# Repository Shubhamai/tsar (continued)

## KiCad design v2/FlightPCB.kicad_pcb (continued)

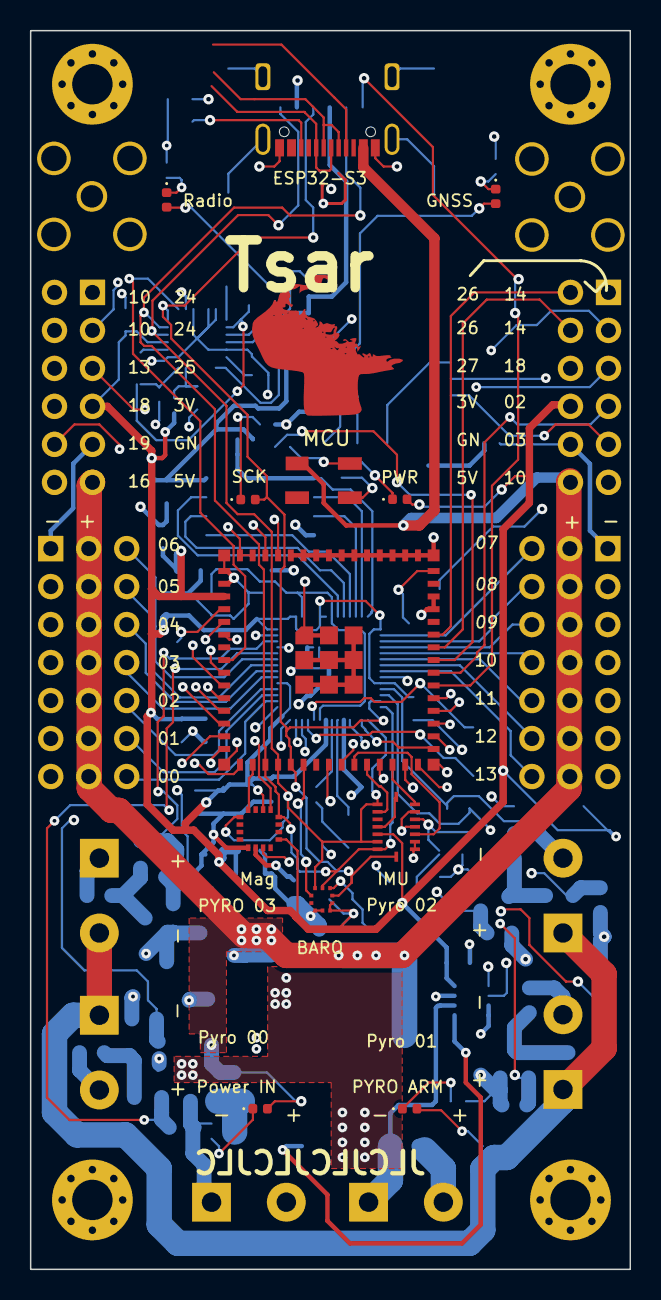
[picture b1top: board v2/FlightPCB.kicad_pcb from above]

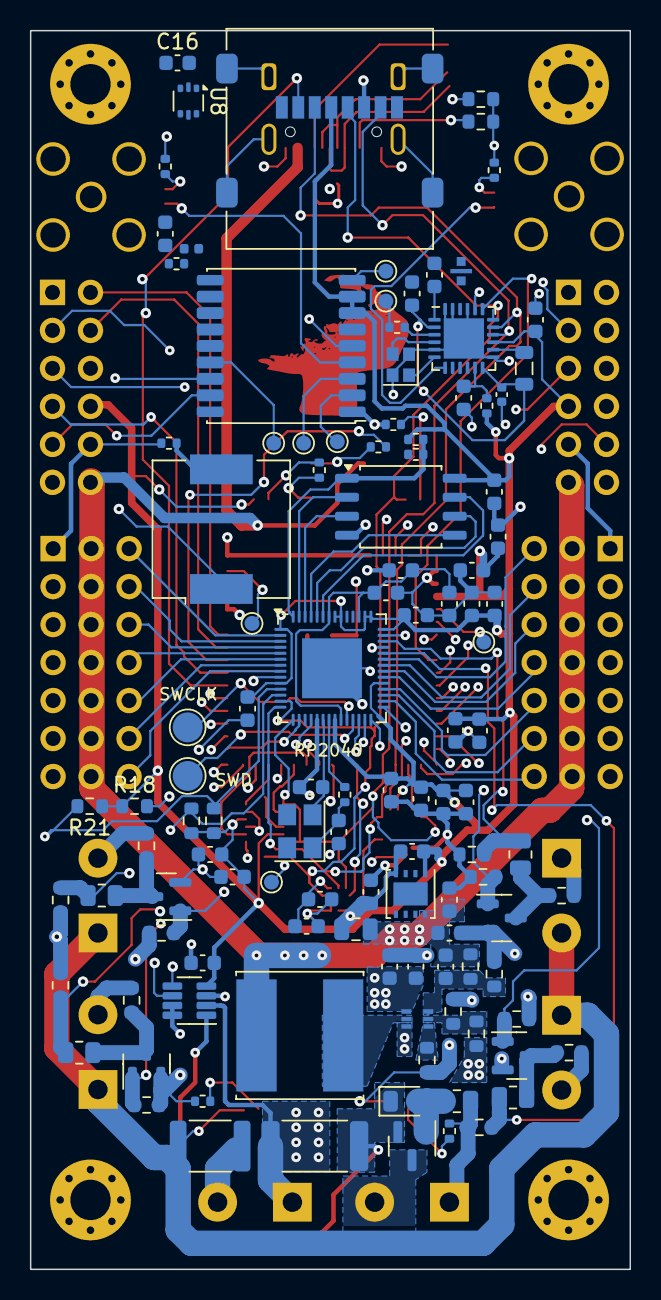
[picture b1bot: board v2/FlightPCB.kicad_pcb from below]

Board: 4 copper layers, 40.1 x 82.8 mm, 142 parts (114 on the bottom side), 124 nets.

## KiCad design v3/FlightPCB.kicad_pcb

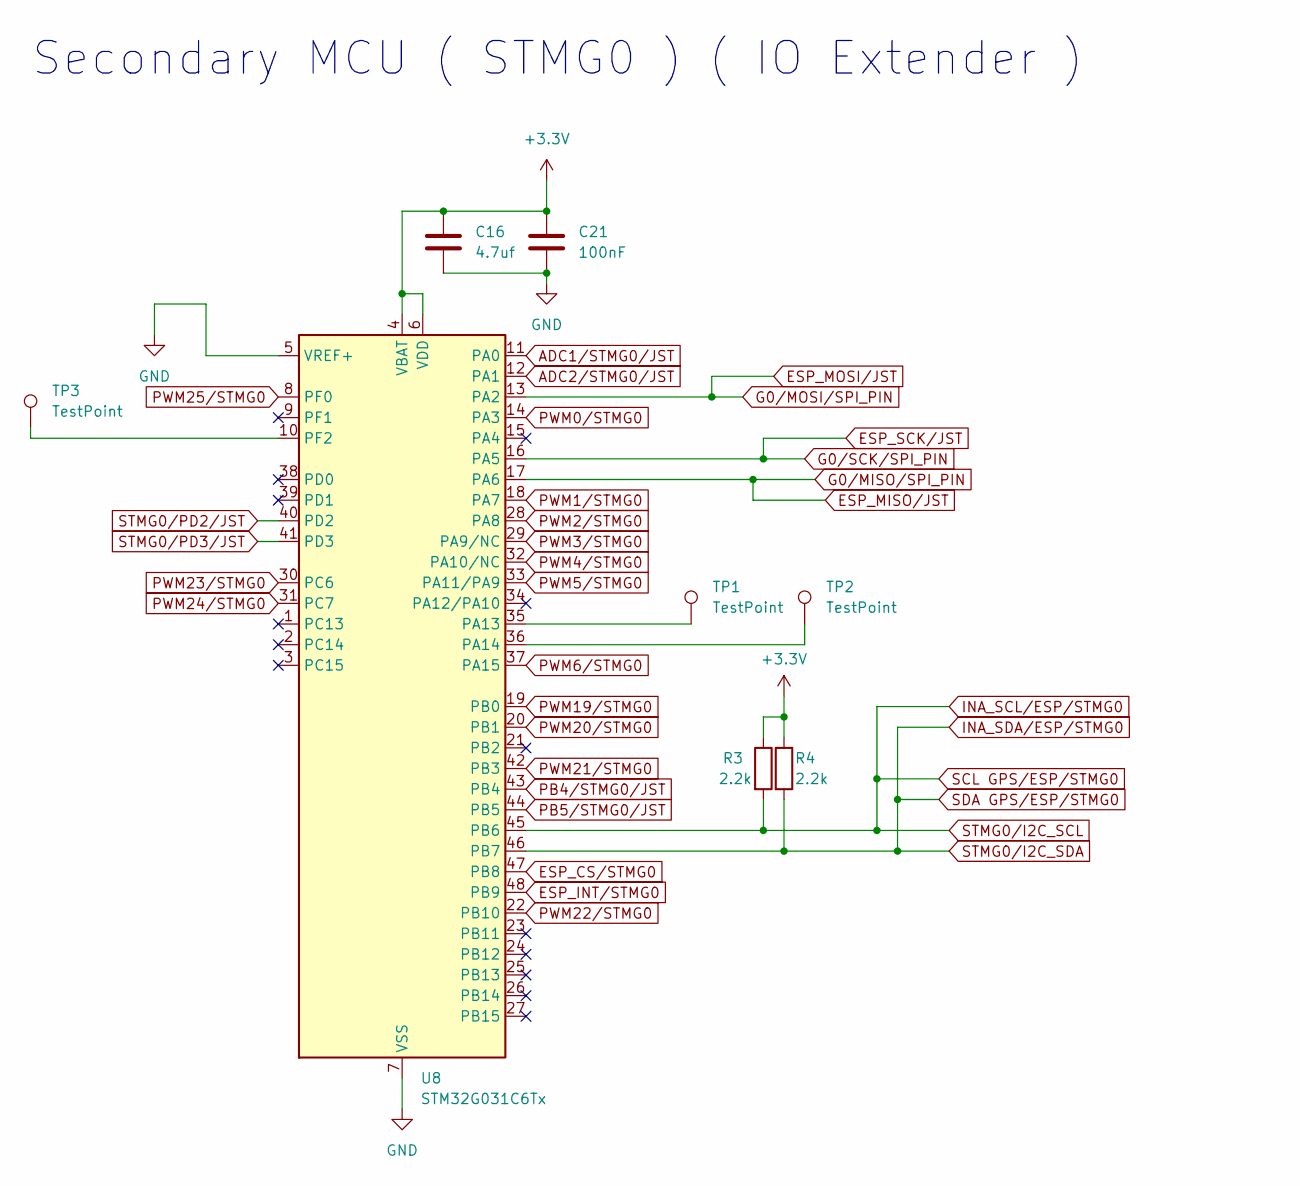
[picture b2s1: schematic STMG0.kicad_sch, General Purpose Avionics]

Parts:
C16: 4.7uf; C_0402_1005Metric
C21: 100nF; C_0402_1005Metric
R3, R4: 2.2k; R_0603_1608Metric
TP1, TP2, TP3: TestPoint; TestPoint_Pad_D1.0mm
U8: STM32G031C6Tx; LQFP-48_7x7mm_P0.5mm

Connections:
+3.3V: C16.1, C21.1, R3.1, R4.1, U8.4 (VBAT), U8.6 (VDD); also elsewhere on the board
ADC1/STMG0/JST: U8.11 (PA0); also elsewhere on the board
ADC2/STMG0/JST: U8.12 (PA1); also elsewhere on the board
BARO_MISO/ESP: U8.17 (PA6); also elsewhere on the board
BARO_MOSI/ESP: U8.13 (PA2); also elsewhere on the board
BARO_SCK/ESP: U8.16 (PA5); also elsewhere on the board
BatteryTerminal-: C16.2, C21.2, U8.5 (VREF+), U8.7 (VSS); also elsewhere on the board
ESP_CS/STMG0: U8.47 (PB8); also elsewhere on the board
ESP_INT/STMG0: U8.48 (PB9); also elsewhere on the board
ESP_SCL/Headers/JST: R3.2, U8.45 (PB6); also elsewhere on the board
ESP_SDA/Headers/JST: R4.2, U8.46 (PB7); also elsewhere on the board
unnamed: TP1.1, U8.35 (PA13)
unnamed: TP2.1, U8.36 (PA14)
unnamed: TP3.1, U8.10 (PF2)
PB4/STMG0/JST: U8.43 (PB4); also elsewhere on the board
PB5/STMG0/JST: U8.44 (PB5); also elsewhere on the board
PWM0/STMG0: U8.14 (PA3); also elsewhere on the board
PWM1/STMG0: U8.18 (PA7); also elsewhere on the board
PWM2/STMG0: U8.28 (PA8); also elsewhere on the board
PWM3/STMG0: U8.29 (PA9/NC); also elsewhere on the board
PWM4/STMG0: U8.32 (PA10/NC); also elsewhere on the board
PWM5/STMG0: U8.33 (PA11/PA9); also elsewhere on the board
PWM6/STMG0: U8.37 (PA15); also elsewhere on the board
PWM19/STMG0: U8.19 (PB0); also elsewhere on the board
PWM20/STMG0: U8.20 (PB1); also elsewhere on the board
PWM21/STMG0: U8.42 (PB3); also elsewhere on the board
PWM22/STMG0: U8.22 (PB10); also elsewhere on the board
PWM23/STMG0: U8.30 (PC6); also elsewhere on the board
PWM24/STMG0: U8.31 (PC7); also elsewhere on the board
PWM25/STMG0: U8.8 (PF0); also elsewhere on the board
STMG0/PD2/JST: U8.40 (PD2); also elsewhere on the board
STMG0/PD3/JST: U8.41 (PD3); also elsewhere on the board

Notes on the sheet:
Secondary MCU ( STMG0 ) ( IO Extender )

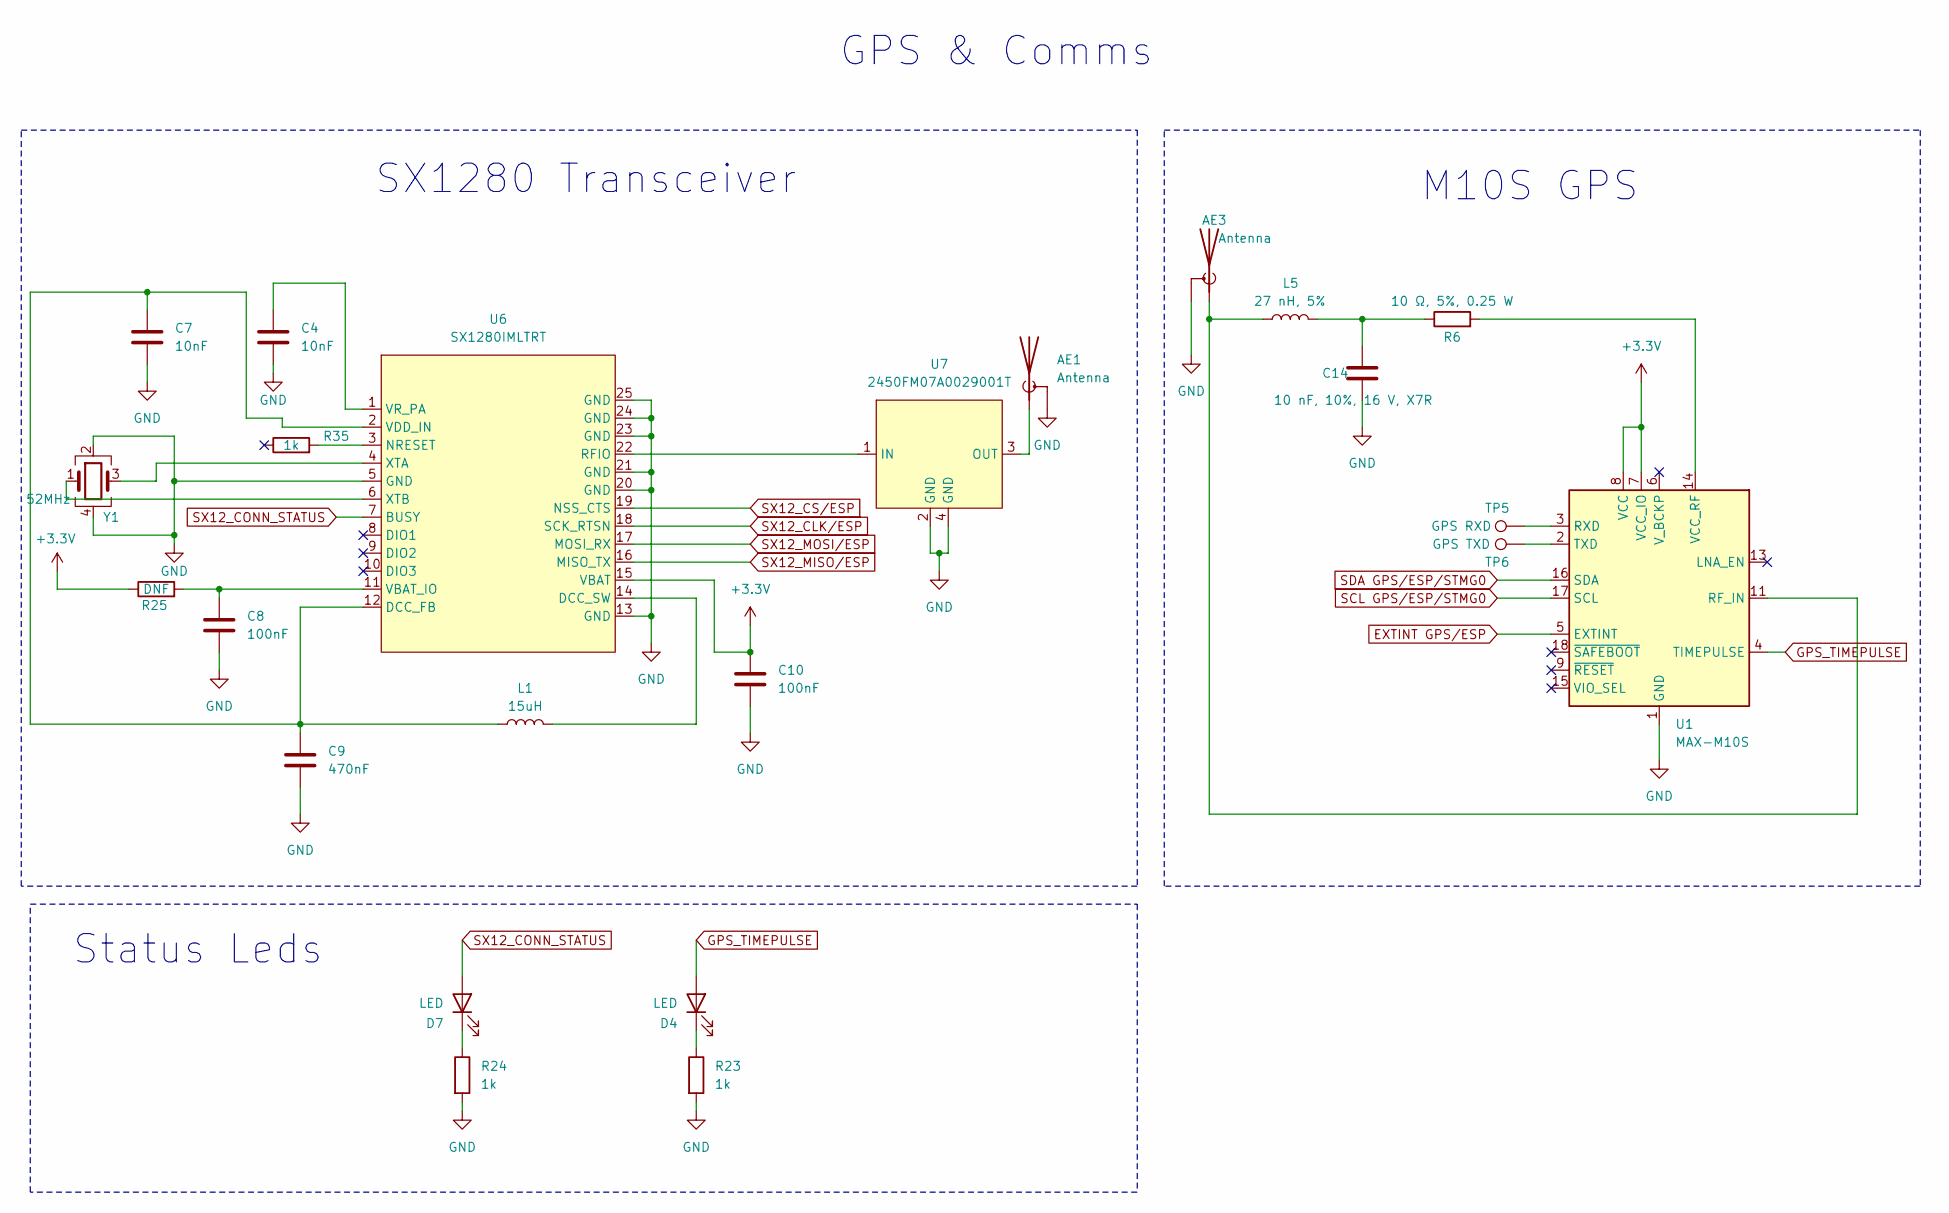
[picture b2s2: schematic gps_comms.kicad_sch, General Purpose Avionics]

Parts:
AE1, AE3: Antenna; SMA_Amphenol_901-144_Vertical
C4, C7: 10nF; C_0603_1608Metric
C8, C10: 100nF; C_0603_1608Metric
C9: 470nF; C_0402_1005Metric
C14: 10 nF, 10%, 16 V, X7R; C_0603_1608Metric
D4, D7: LED; LED_0402_1005Metric
L1: 15uH; L_0805_2012Metric
L5: 27 nH, 5%; L_0402_1005Metric
R6: 10 Ω, 5%, 0.25 W; R_0402_1005Metric
R23, R24, R35: 1k; R_0402_1005Metric
R25: DNF; R_0402_1005Metric
TP5: GPS RXD; TestPoint_Pad_D1.0mm
TP6: GPS TXD; TestPoint_Pad_D1.0mm
U1: MAX-M10S; ublox_MAX
U6: SX1280IMLTRT; QFN-24-1EP_4x4mm_P0.5mm_EP2.7x2.7mm
U7: 2450FM07A0029001T
Y1: 52MHz; Crystal_SMD_2016-4Pin_2.0x1.6mm

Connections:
+3.3V: C10.1, R25.1, U1.7 (VCC_IO), U1.8 (VCC), U6.15 (VBAT); also elsewhere on the board
BARO_MISO/ESP: U6.16 (MISO_TX); also elsewhere on the board
BARO_MOSI/ESP: U6.17 (MOSI_RX); also elsewhere on the board
BARO_SCK/ESP: U6.18 (SCK_RTSN); also elsewhere on the board
BatteryTerminal-: AE1.2 (Shield), AE3.2 (Shield), C4.2, C7.2, C8.2, C9.2, C10.2, C14.1, R23.2, R24.2, U1.1 (GND), U1.10 (GND), U1.12 (GND), U6.5 (GND), U6.13 (GND), U6.20 (GND), U6.21 (GND), U6.23 (GND), U6.24 (GND), U6.25 (GND), U7.2 (GND), U7.4 (GND), Y1.2, Y1.4; also elsewhere on the board
ESP_SCL/Headers/JST: U1.17 (SCL); also elsewhere on the board
ESP_SDA/Headers/JST: U1.16 (SDA); also elsewhere on the board
EXTINT GPS/ESP: U1.5 (EXTINT); also elsewhere on the board
GPS_TIMEPULSE: D4.2 (A), U1.4 (TIMEPULSE)
unnamed: AE1.1 (A), U7.3 (OUT)
unnamed: AE3.1 (A), L5.1, U1.11 (RF_IN)
unnamed: C14.2, L5.2, R6.1
unnamed: D4.1 (K), R23.1
unnamed: D7.1 (K), R24.1
unnamed: TP5.1, U1.3 (RXD)
unnamed: TP6.1, U1.2 (TXD)
unnamed: R6.2, U1.14 (VCC_RF)
unnamed: C7.1, C9.1, L1.1, U6.2 (VDD_IN), U6.12 (DCC_FB)
unnamed: L1.2, U6.14 (DCC_SW)
unnamed: R35.2, U6.3 (NRESET)
unnamed: U6.22 (RFIO), U7.1 (IN)
unnamed: C8.1, R25.2, U6.11 (VBAT_IO)
unnamed: C4.1, U6.1 (VR_PA)
unnamed: U6.4 (XTA), Y1.3
unnamed: U6.6 (XTB), Y1.1
SX12_CONN_STATUS: D7.2 (A), U6.7 (BUSY)
SX12_CS/ESP: U6.19 (NSS_CTS); also elsewhere on the board

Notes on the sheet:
GPS & Comms
M10S GPS
Status Leds
SX1280 Transceiver

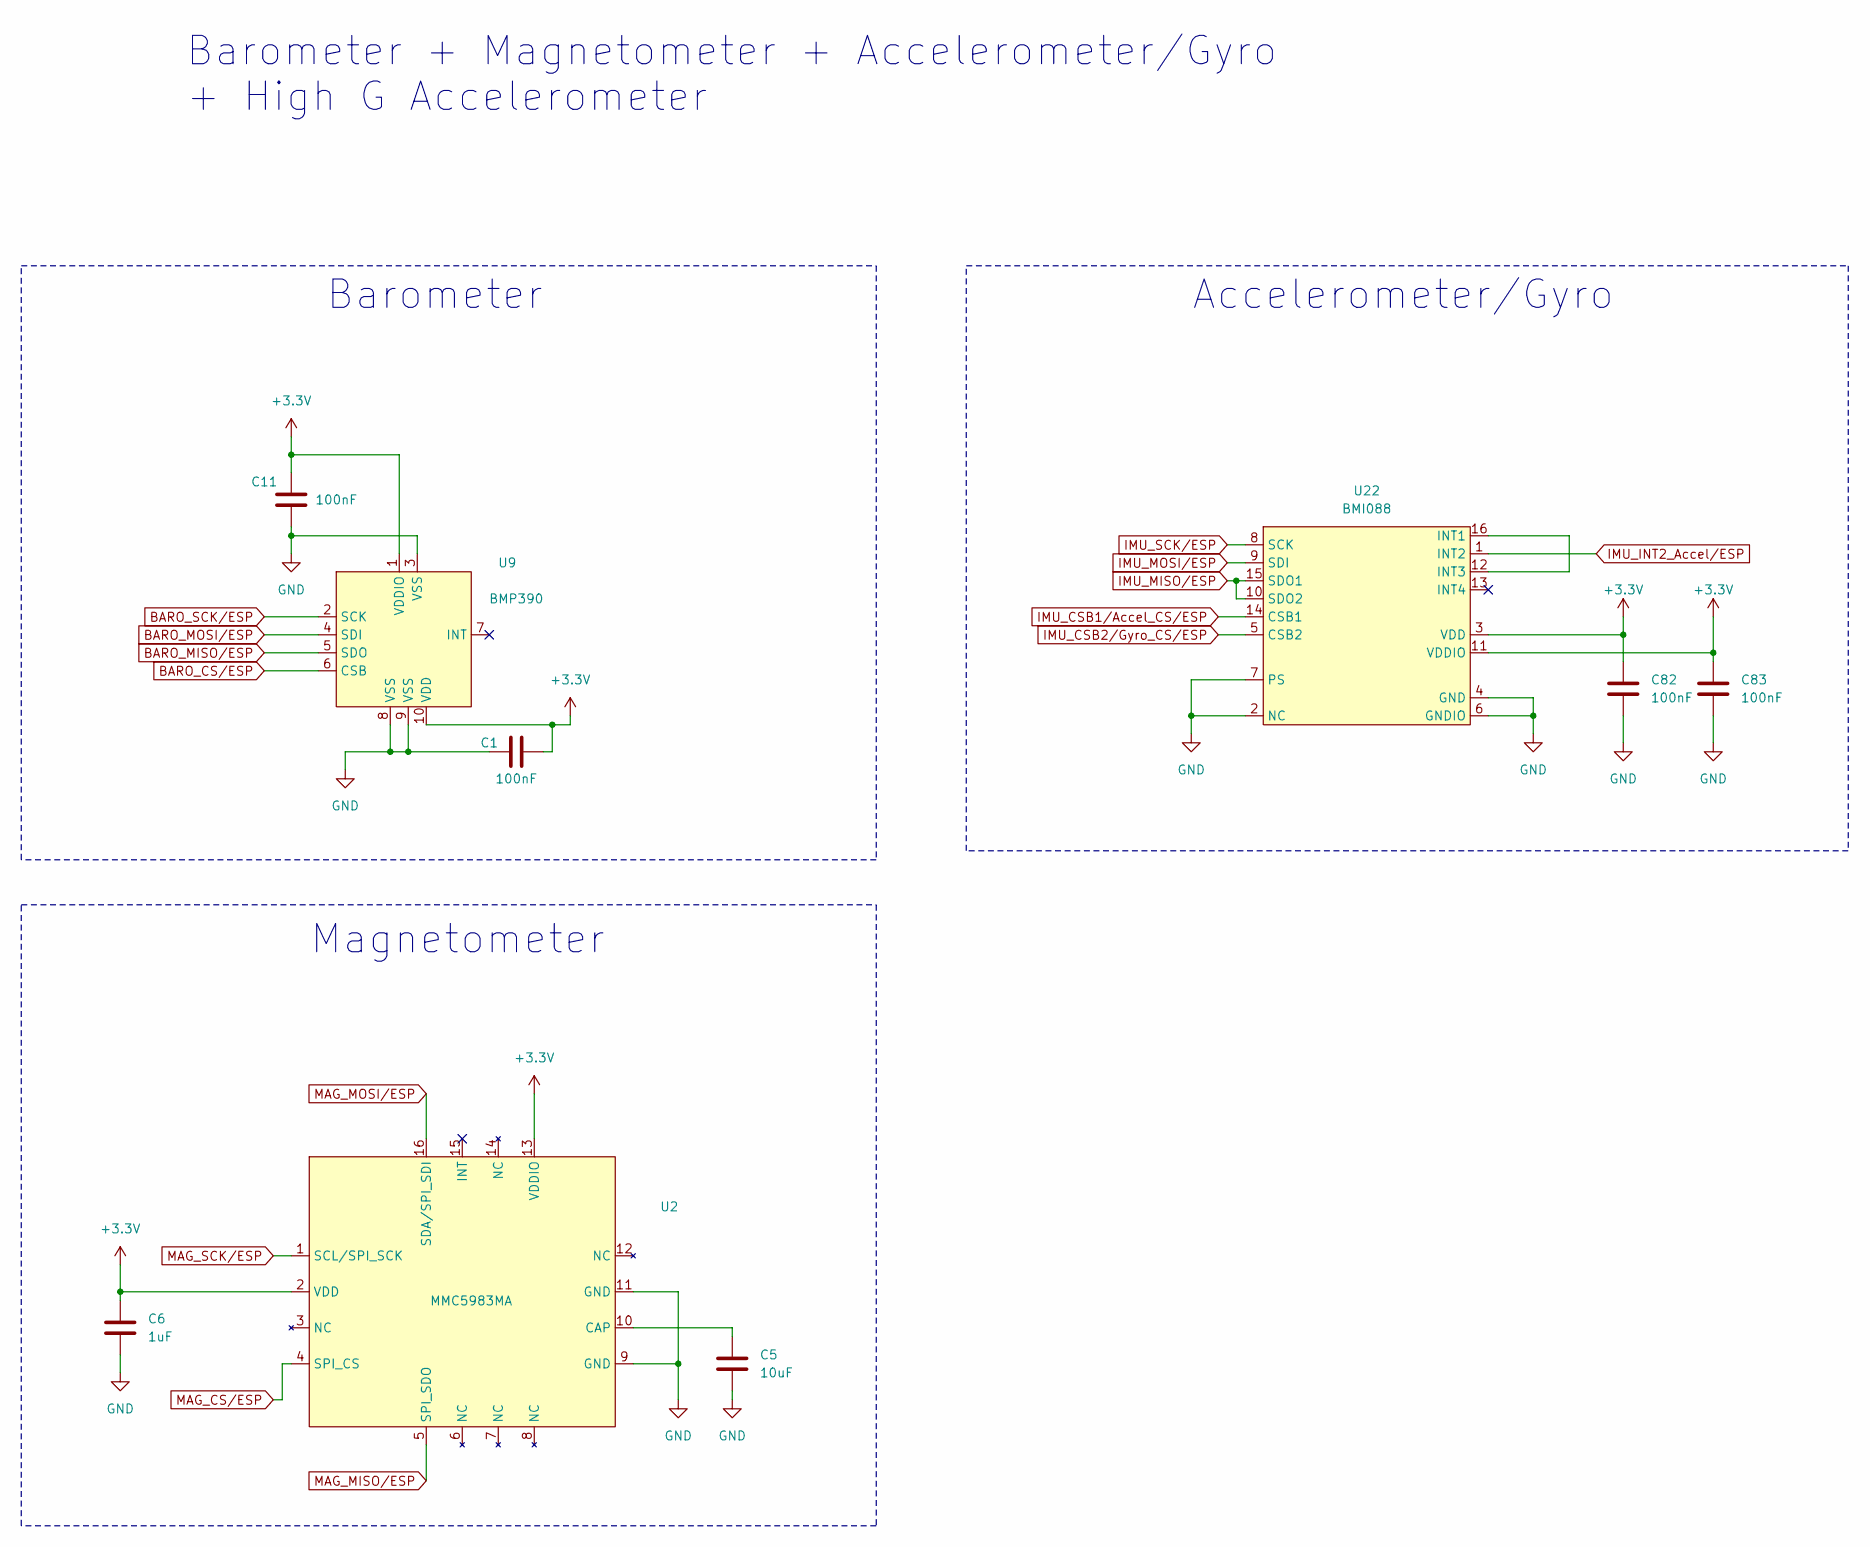
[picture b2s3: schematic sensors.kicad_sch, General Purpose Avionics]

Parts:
C1, C11, C82, C83: 100nF; C_0603_1608Metric
C5: 10uF; C_0603_1608Metric
C6: 1uF; C_0603_1608Metric
U2: MMC5983MA
U9: BMP390
U22: BMI088

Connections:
+3.3V: C1.2, C6.1, C11.2, C82.1, C83.1, U2.2 (VDD), U2.13 (VDDIO), U9.1 (VDDIO), U9.10 (VDD), U22.3 (VDD), U22.11 (VDDIO); also elsewhere on the board
BARO_CS/ESP: U9.6 (CSB); also elsewhere on the board
BARO_MISO/ESP: U2.5 (SPI_SDO), U9.5 (SDO), U22.10 (SDO2), U22.15 (SDO1); also elsewhere on the board
BARO_MOSI/ESP: U2.16 (SDA/SPI_SDI), U9.4 (SDI), U22.9 (SDI); also elsewhere on the board
BARO_SCK/ESP: U2.1 (SCL/SPI_SCK), U9.2 (SCK), U22.8 (SCK); also elsewhere on the board
BatteryTerminal-: C1.1, C5.2, C6.2, C11.1, C82.2, C83.2, U2.9 (GND), U2.11 (GND), U9.3 (VSS), U9.8 (VSS), U9.9 (VSS), U22.2 (NC), U22.4 (GND), U22.6 (GNDIO), U22.7 (PS); also elsewhere on the board
IMU_CSB1/Accel_CS/ESP: U22.14 (CSB1); also elsewhere on the board
IMU_CSB2/Gyro_CS/ESP: U22.5 (CSB2); also elsewhere on the board
IMU_INT2_Accel/ESP: U22.1 (INT2); also elsewhere on the board
MAG_CS/ESP: U2.4 (SPI_CS); also elsewhere on the board
unnamed: C5.1, U2.10 (CAP)
unnamed: U22.12 (INT3), U22.16 (INT1)

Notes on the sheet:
Accelerometer/Gyro
Magnetometer
Barometer
Barometer + Magnetometer + Accelerometer/Gyro + High G Accelerometer

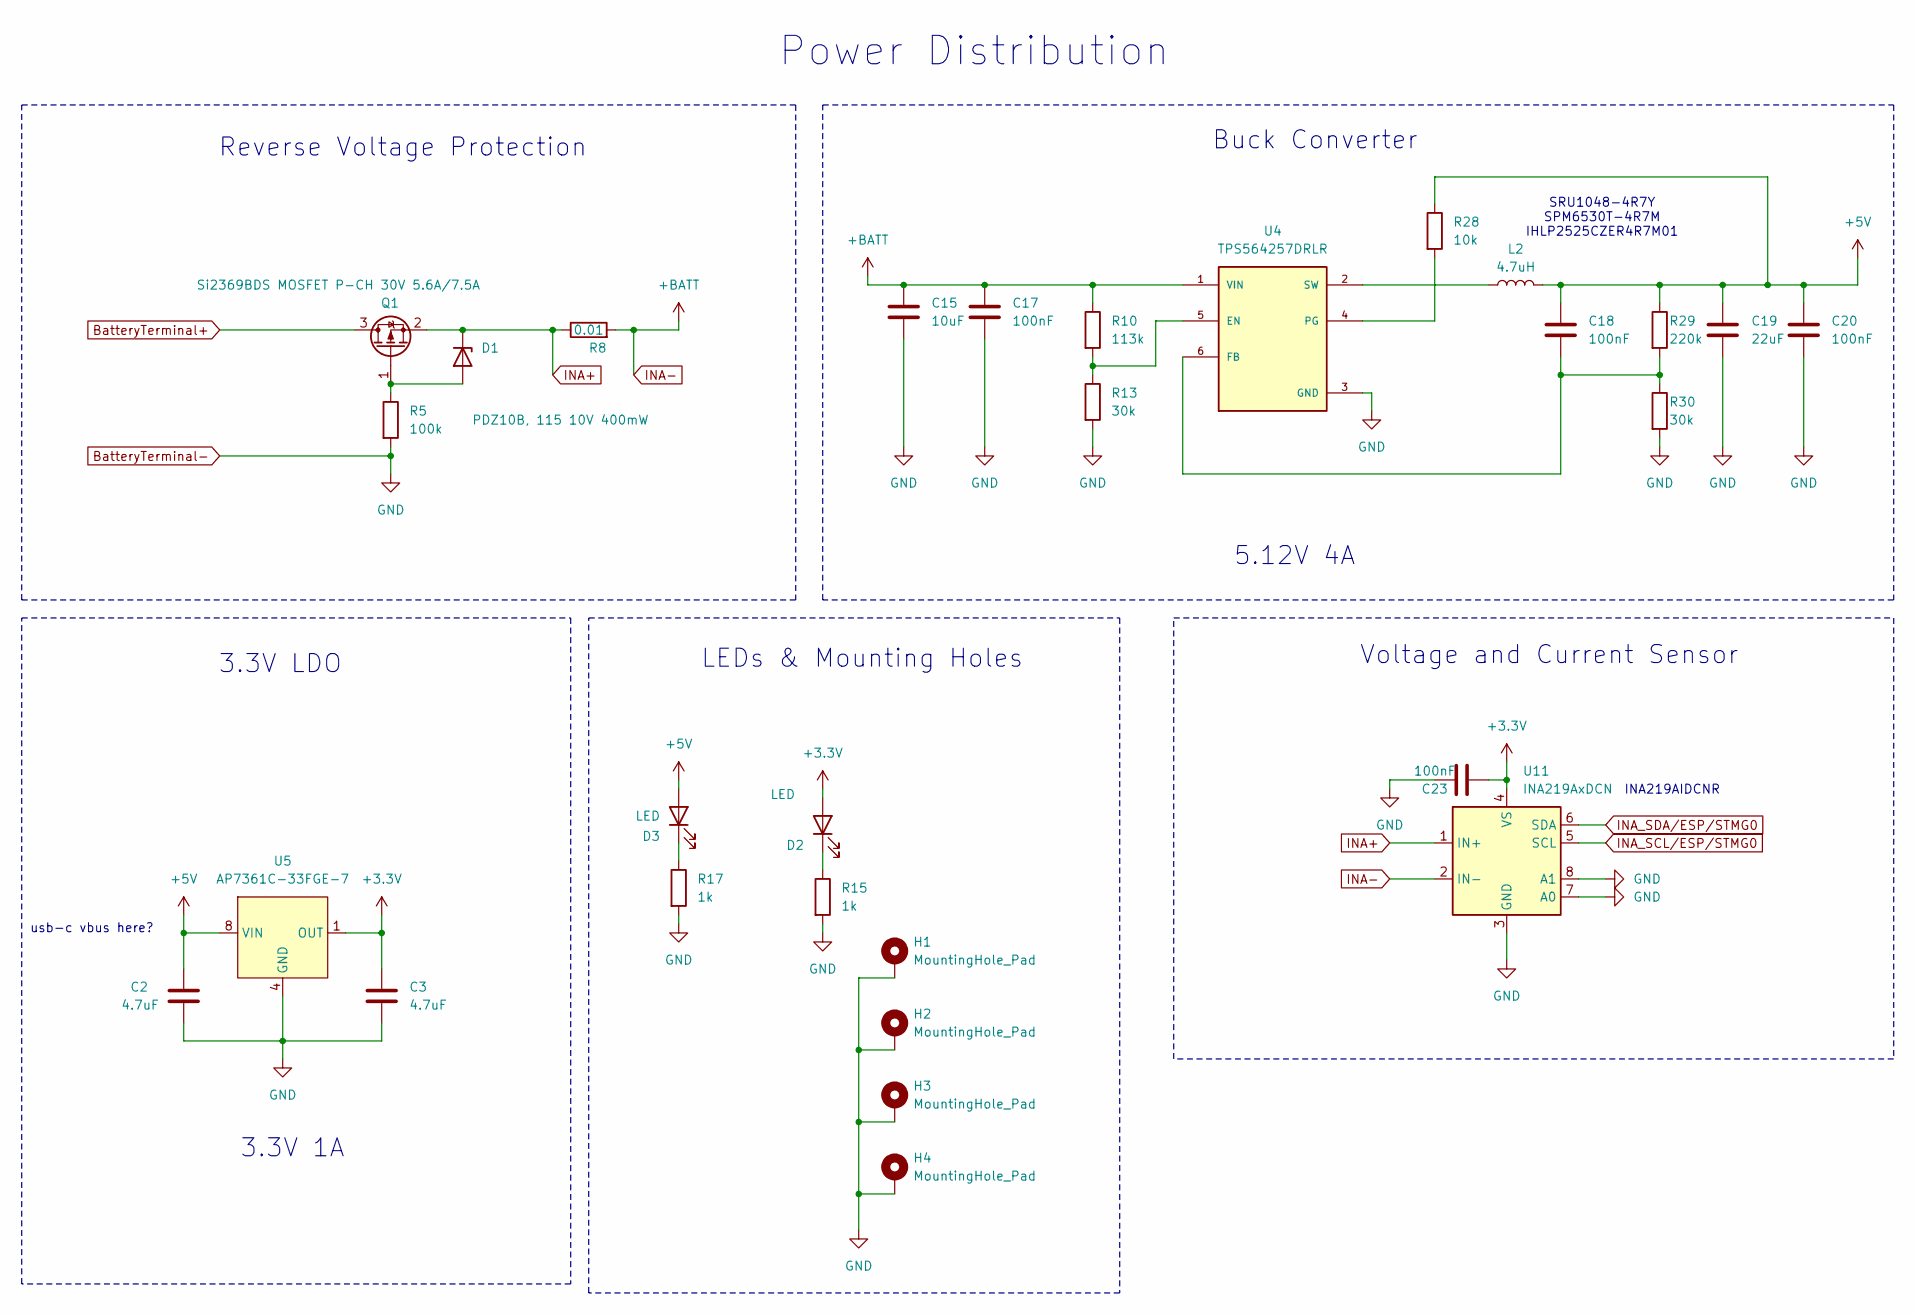
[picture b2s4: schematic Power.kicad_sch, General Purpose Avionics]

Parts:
C2, C3: 4.7uF; C_0603_1608Metric
C15: 10uF; C_0603_1608Metric
C17, C18, C20, C23: 100nF; C_0603_1608Metric
C19: 22uF; C_0805_2012Metric
D1: PDZ10B, 115 10V 400mW; D_0805_2012Metric
D2, D3: LED; LED_0402_1005Metric
H1, H2, H3, H4: MountingHole_Pad; MountingHole_2.7mm_M2.5_Pad_Via
L2: 4.7uH; L_Cenker_CKCS8040
Q1: Si2369BDS MOSFET P-CH 30V 5.6A/7.5A; SOT-23
R5: 100k; R_0805_2012Metric
R8: 0.01; R_2512_6332Metric
R10: 113k; R_0603_1608Metric
R13, R30: 30k; R_0603_1608Metric
R15, R17: 1k; R_0402_1005Metric
R28: 10k; R_0603_1608Metric
R29: 220k; R_0603_1608Metric
U4: TPS564257DRLR; SOT50P160X60-6N; PARTREV A
U5: AP7361C-33FGE-7; MLF-8-1EP_3x3mm_P0.65mm_EP1.55x2.3mm
U11: INA219AxDCN; SOT-23-8

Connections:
+3.3V: C3.1, C23.2, D2.2 (A), U5.1 (OUT), U11.4 (VS); also elsewhere on the board
+5V: C2.1, C18.1, C19.1, C20.1, D3.2 (A), L2.2, R28.1, R29.1, U5.8 (VIN); also elsewhere on the board
BatteryTerminal+: Q1.3 (D); also elsewhere on the board
BatteryTerminal-: C2.2, C3.2, C15.2, C17.2, C19.2, C20.2, C23.1, H1.1, H2.1, H3.1, H4.1, R5.2, R13.2, R15.2, R17.2, R30.2, U4.3 (GND), U5.4 (GND), U11.3 (GND), U11.7 (A0), U11.8 (A1); also elsewhere on the board
ESP_SCL/Headers/JST: U11.5 (SCL); also elsewhere on the board
ESP_SDA/Headers/JST: U11.6 (SDA); also elsewhere on the board
INA+: D1.1 (K), Q1.2 (S), R8.1, U11.1 (IN+)
INA-: C15.1, C17.1, R8.2, R10.1, U4.1 (VIN), U11.2 (IN-); also elsewhere on the board
unnamed: D1.2 (A), Q1.1 (G), R5.1
unnamed: D2.1 (K), R15.1
unnamed: D3.1 (K), R17.1
unnamed: R10.2, R13.1, U4.5 (EN)
unnamed: C18.2, R29.2, R30.1, U4.6 (FB)
unnamed: R28.2, U4.4 (PG)
unnamed: L2.1, U4.2 (SW)

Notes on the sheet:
INA219AIDCNR
3.3V LDO
SRU1048-4R7Y SPM6530T-4R7M IHLP2525CZER4R7M01
Voltage and Current Sensor
3.3V 1A
Reverse Voltage Protection
5.12V 4A
LEDs & Mounting Holes
Power Distribution
Buck Converter
usb-c vbus here?

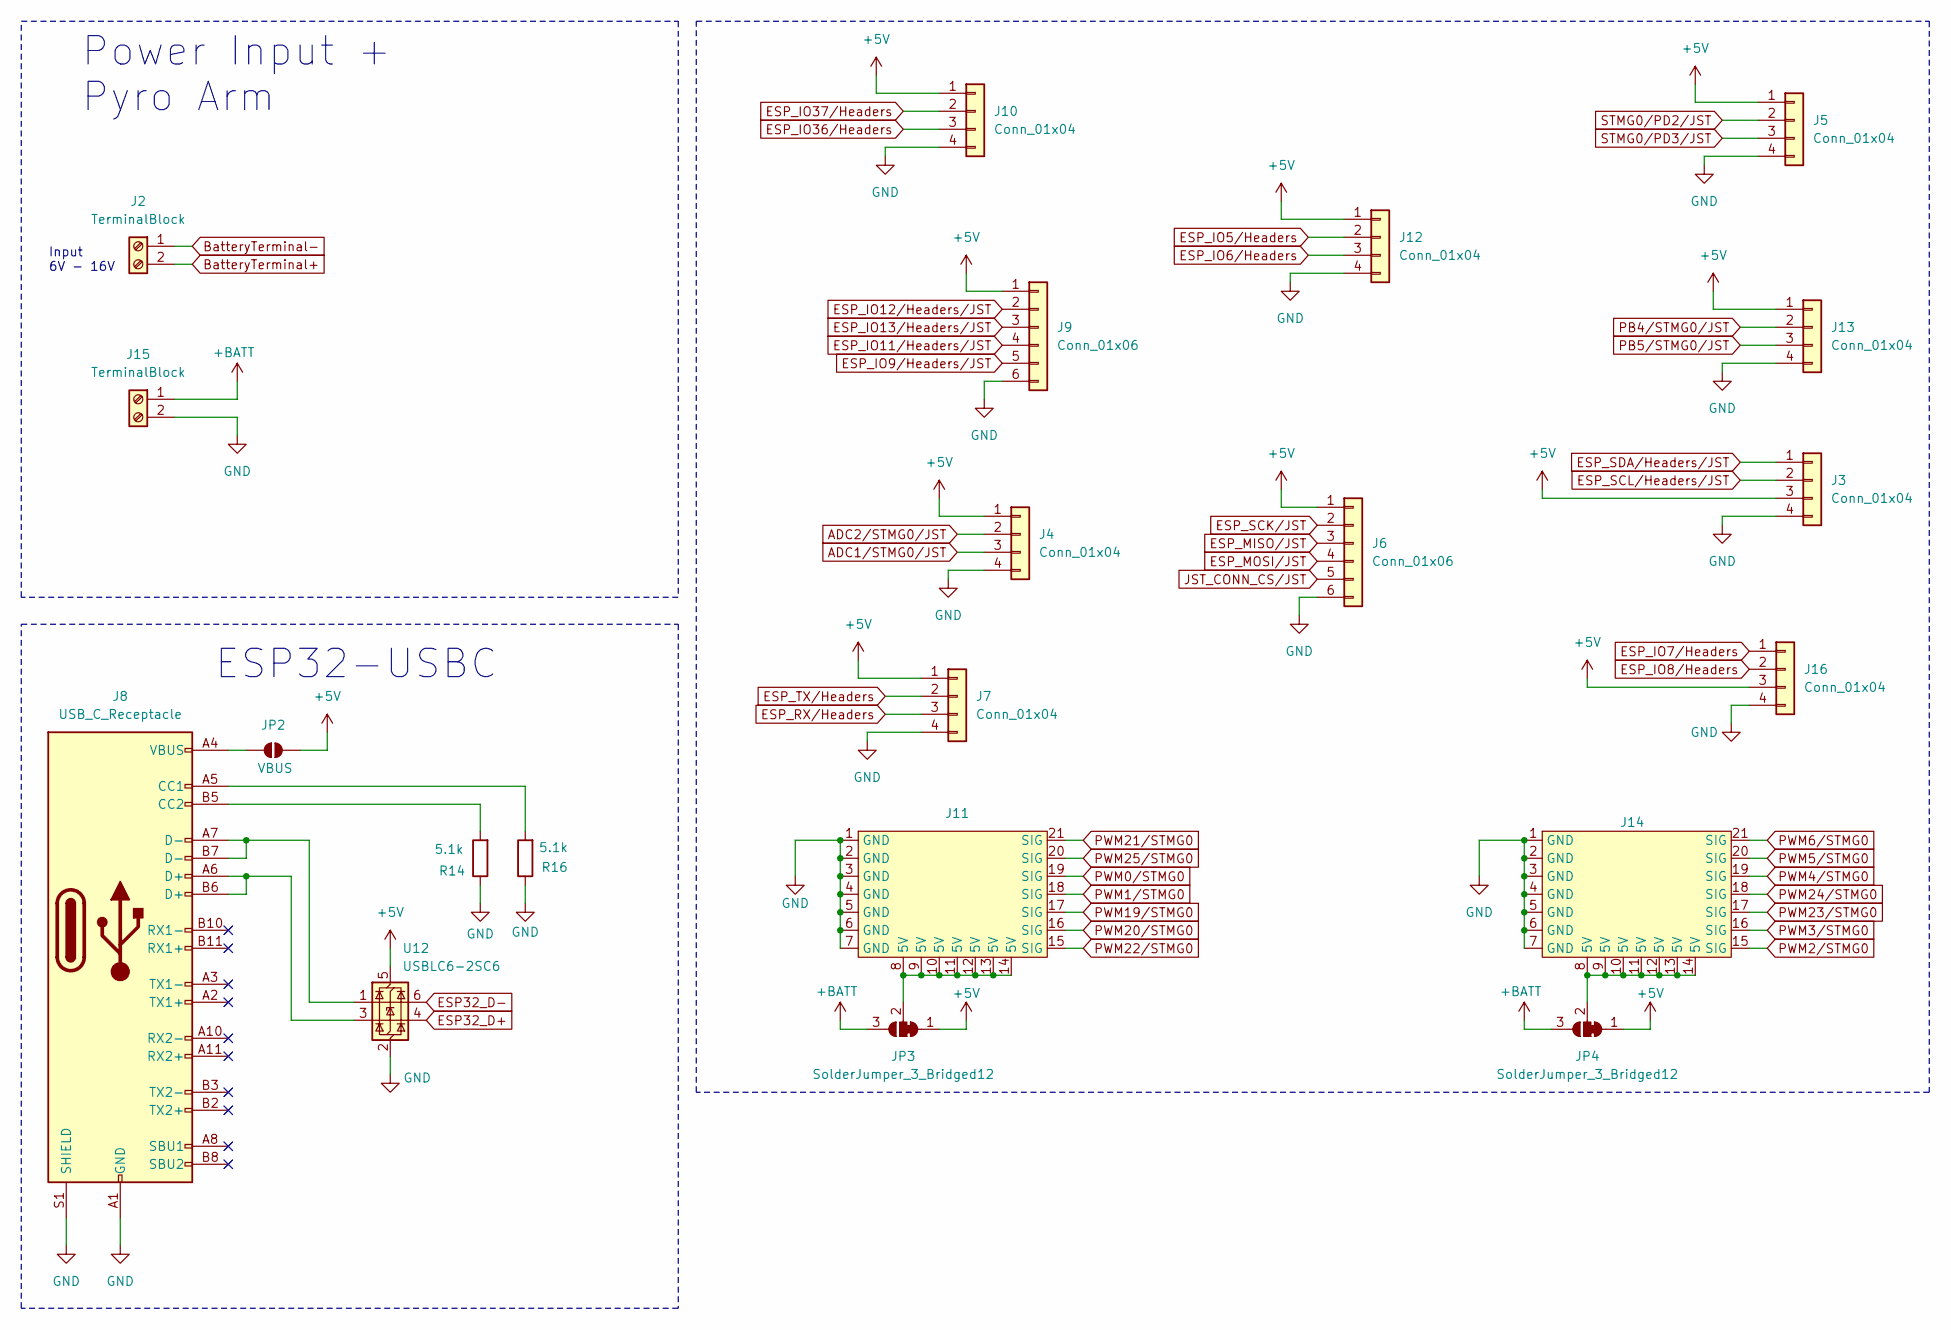
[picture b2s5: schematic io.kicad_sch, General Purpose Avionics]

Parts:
J2, J15: TerminalBlock; TerminalBlock_Phoenix_PT-1,5-2-5.0-H_1x02_P5.00mm_Horizontal
J3, J16: Conn_01x04; JST_SH_BM04B-SRSS-TB_1x04-1MP_P1.00mm_Vertical
J4, J5, J7, J10, J12, J13: Conn_01x04; Hirose_DF13-04P-1.25DSA_1x04_P1.25mm_Vertical
J6, J9: Conn_01x06; Hirose_DF13-06P-1.25DSA_1x06_P1.25mm_Vertical
J8: USB_C_Receptacle; USB_C_Receptacle_GCT_USB4105-xx-A_16P_TopMnt_Horizontal
J11: PinHeader_3x05_P2.54mm_Vertical_Left
J14: PinHeader_3x05_P2.54mm_Vertical_Right
JP2: VBUS; SolderJumper-2_P1.3mm_Open_TrianglePad1.0x1.5mm
JP3, JP4: SolderJumper_3_Bridged12; SolderJumper-3_P1.3mm_Bridged12_Pad1.0x1.5mm_NumberLabels
R14, R16: 5.1k; R_0603_1608Metric
U12: USBLC6-2SC6; SOT-23-6

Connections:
+5V: J3.3, J4.1, J5.1, J6.1, J7.1, J9.1, J10.1, J12.1, J13.1, J16.3, JP2.2 (B), JP3.1 (A), JP4.1 (A), U12.5 (VBUS); also elsewhere on the board
ADC1/STMG0/JST: J4.3; also elsewhere on the board
ADC2/STMG0/JST: J4.2; also elsewhere on the board
BARO_MISO/ESP: J6.3; also elsewhere on the board
BARO_MOSI/ESP: J6.4; also elsewhere on the board
BARO_SCK/ESP: J6.2; also elsewhere on the board
BatteryTerminal+: J2.2; also elsewhere on the board
BatteryTerminal-: J2.1, J3.4, J4.4, J5.4, J6.6, J7.4, J8.A1 (GND), J8.A12 (GND), J8.B1 (GND), J8.B12 (GND), J8.S1 (SHIELD), J9.6, J10.4, J11.1 (GND), J11.2 (GND), J11.3 (GND), J11.4 (GND), J11.5 (GND), J11.6 (GND), J11.7 (GND), J12.4, J13.4, J14.1 (GND), J14.2 (GND), J14.3 (GND), J14.4 (GND), J14.5 (GND), J14.6 (GND), J14.7 (GND), J15.2, J16.4, R14.1, R16.1, U12.2 (GND); also elsewhere on the board
ESP32_D+: U12.4 (I/O2); also elsewhere on the board
ESP32_D-: U12.6 (I/O1); also elsewhere on the board
ESP_IO5/Headers: J12.2; also elsewhere on the board
ESP_IO6/Headers: J12.3; also elsewhere on the board
ESP_IO7/Headers: J16.1; also elsewhere on the board
ESP_IO8/Headers: J16.2; also elsewhere on the board
ESP_IO9/Headers/JST: J9.5; also elsewhere on the board
ESP_IO11/Headers/JST: J9.4; also elsewhere on the board
ESP_IO12/Headers/JST: J9.2; also elsewhere on the board
ESP_IO13/Headers/JST: J9.3; also elsewhere on the board
ESP_IO36/Headers: J10.3; also elsewhere on the board
ESP_IO37/Headers: J10.2; also elsewhere on the board
ESP_RX/Headers: J7.3; also elsewhere on the board
ESP_SCL/Headers/JST: J3.2; also elsewhere on the board
ESP_SDA/Headers/JST: J3.1; also elsewhere on the board
ESP_TX/Headers: J7.2; also elsewhere on the board
INA-: J15.1, JP3.3 (B), JP4.3 (B); also elsewhere on the board
JST_CONN_CS/JST: J6.5; also elsewhere on the board
unnamed: J8.A5 (CC1), R16.2
unnamed: J8.B5 (CC2), R14.2
unnamed: J8.A6 (D+), J8.B6 (D+), U12.3 (I/O2)
unnamed: J8.A7 (D-), J8.B7 (D-), U12.1 (I/O1)
unnamed: J8.A4 (VBUS), J8.A9 (VBUS), J8.B4 (VBUS), J8.B9 (VBUS), JP2.1 (A)
unnamed: J11.8 (5V), J11.9 (5V), J11.10 (5V), J11.11 (5V), J11.12 (5V), J11.13 (5V), J11.14 (5V), JP3.2 (C)
unnamed: J14.8 (5V), J14.9 (5V), J14.10 (5V), J14.11 (5V), J14.12 (5V), J14.13 (5V), J14.14 (5V), JP4.2 (C)
PB4/STMG0/JST: J13.2; also elsewhere on the board
PB5/STMG0/JST: J13.3; also elsewhere on the board
PWM0/STMG0: J11.19 (SIG); also elsewhere on the board
PWM1/STMG0: J11.18 (SIG); also elsewhere on the board
PWM2/STMG0: J14.15 (SIG); also elsewhere on the board
PWM3/STMG0: J14.16 (SIG); also elsewhere on the board
PWM4/STMG0: J14.19 (SIG); also elsewhere on the board
PWM5/STMG0: J14.20 (SIG); also elsewhere on the board
PWM6/STMG0: J14.21 (SIG); also elsewhere on the board
PWM19/STMG0: J11.17 (SIG); also elsewhere on the board
PWM20/STMG0: J11.16 (SIG); also elsewhere on the board
PWM21/STMG0: J11.21 (SIG); also elsewhere on the board
PWM22/STMG0: J11.15 (SIG); also elsewhere on the board
PWM23/STMG0: J14.17 (SIG); also elsewhere on the board
PWM24/STMG0: J14.18 (SIG); also elsewhere on the board
PWM25/STMG0: J11.20 (SIG); also elsewhere on the board
STMG0/PD2/JST: J5.2; also elsewhere on the board
STMG0/PD3/JST: J5.3; also elsewhere on the board

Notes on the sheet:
Input 6V - 16V
ESP32-USBC
Power Input + Pyro Arm
